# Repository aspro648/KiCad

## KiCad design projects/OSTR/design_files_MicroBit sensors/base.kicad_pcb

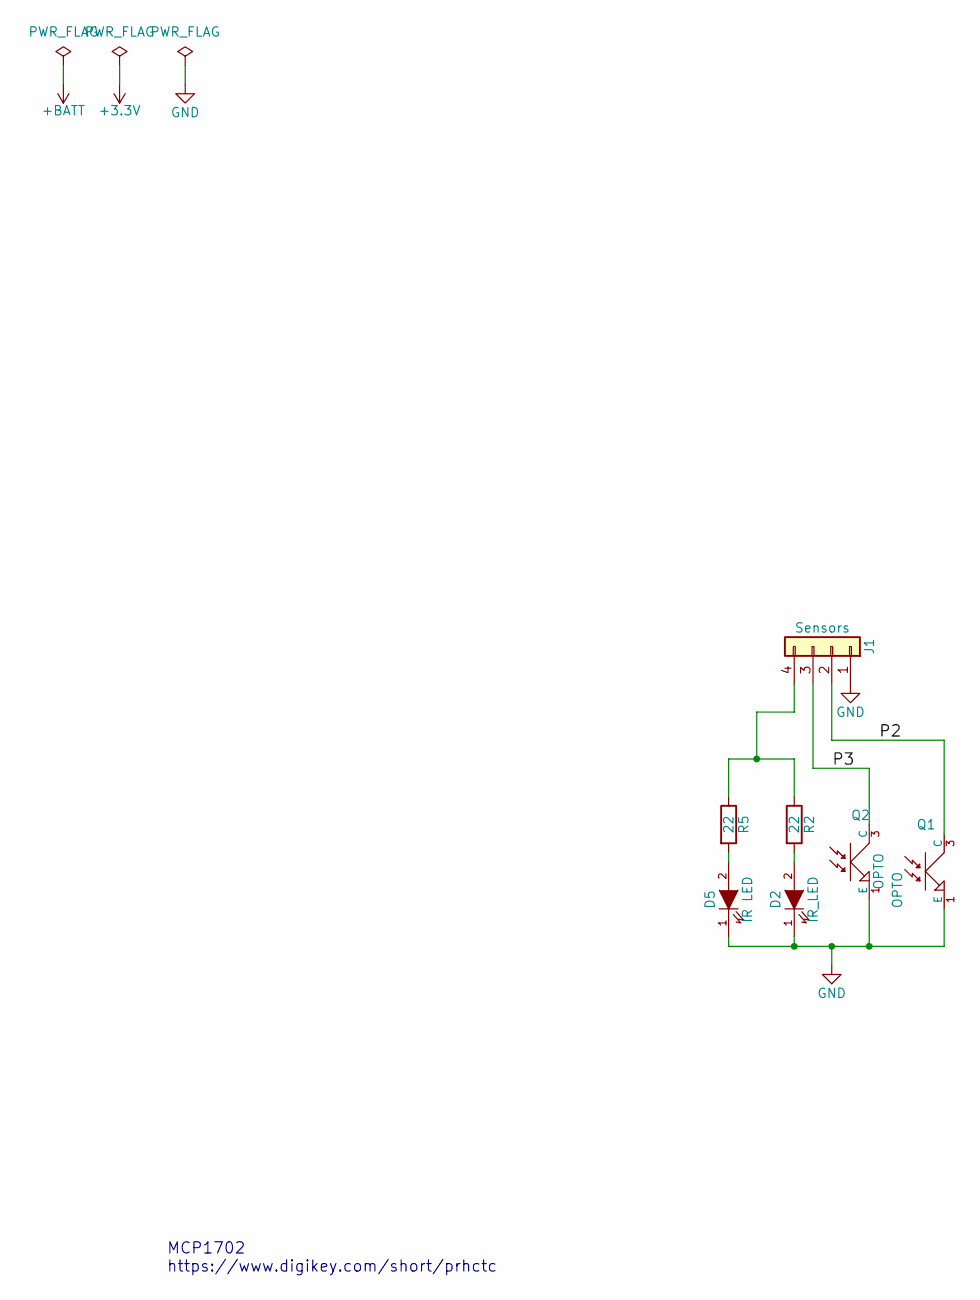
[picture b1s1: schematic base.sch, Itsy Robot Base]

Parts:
D2: IR_LED; LED-3MM
D5: IR LED; LED-3MM
J1: Sensors; Pin_Header_Straight_1x04_Pitch2.54mm
Q1, Q2: OPTO; PHOTOTRANS
R2, R5: 22; Resistor_Horz

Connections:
/P2: J1.2, Q1.3 (C)
/P3: J1.3, Q2.3 (C)
GND: D2.1 (K), D5.1 (K), J1.1, Q1.1 (E), Q2.1 (E)
unnamed: D2.2 (A), R2.2
unnamed: D5.2 (A), R5.2
unnamed: J1.4, R2.1, R5.1

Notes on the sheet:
MCP1702 https://www.digikey.com/short/prhctc

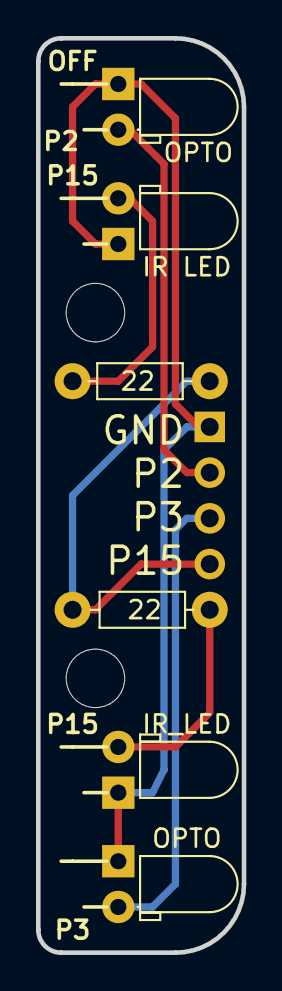
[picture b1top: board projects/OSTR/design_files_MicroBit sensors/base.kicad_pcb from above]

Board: 2 copper layers, 11.4 x 50.8 mm, 9 parts (1 on the bottom side), 6 nets.

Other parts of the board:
P9, P9#2: CONN_01X01; Lego_Pad

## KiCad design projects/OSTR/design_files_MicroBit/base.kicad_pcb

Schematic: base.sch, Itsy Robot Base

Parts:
C1: 100uF; C_Radial_D7.5_L11.2_P2.5
C2: 10uF; C_Radial_D5_L11_P2.5
C3, C4: 1uF; C_Disc_D3_P2.5
D1: D; D_A-405_P7.62mm_Horizontal
J1: microbit_edge_connector; MicroBit40
J2: BATT1; TerminalBlock_Pheonix_PT-3.5mm_2pol
J3: BATT2; TerminalBlock_Pheonix_PT-3.5mm_2pol
J4: LEFT_STEPPER; JST_B5B-XH-A
J5: RIGHT_STEPPER; JST_B5B-XH-A
J6: SERVO; Pin_Header_Straight_1x03
J7: TEST; Pin_Header_Straight_1x03_Pitch1.27mm
J8: Sensors; Pin_Header_Straight_1x04_Pitch2.54mm
J9: Sensors; Pin_Header_Angled_1x04_Pitch2.54mm
LS1: Speaker; SPEAKER
Q3: PNP; TO-126_Vertical
Q4: NPN; TO-92_Inline_Wide
R1: 10K; R__7.62mm
R2, R3: 1K; R__7.62mm
SW1: PWR; SW_Micro_SPST
U1: ULN2803; DIP-18_W7.62mm
U2: MCP1702; TO-92_Inline_Wide

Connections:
+3V3: C3.1, J1.17 (P18_3v3), J1.19 (3v3), J1.21 (3v3), J1.23 (3v3), J1.25 (3v3), J1.27 (P17_3v3), J7.2, Q4.3 (C), R1.2, U2.3 (VO)
/BAT: C4.1, D1.1 (K), J7.1, Q3.2, SW1.2, U2.2 (VI)
/P0: J1.71 (P0), J1.73 (P0), J1.75 (P0), J1.77 (P0), U1.1 (1B)
/P1: J1.55 (P1), J1.57 (P1), J1.59 (P1), J1.61 (P1), U1.4 (4B)
/P2: J1.37 (P2), J1.39 (P2), J1.41 (P2), J1.43 (P2), J8.2, J9.2
/P3: J1.79 (P3), J8.3, J9.3
/P4: J1.69 (P4), LS1.1
/P6: J1.65 (P6), U1.2 (2B)
/P7: J1.63 (P7), U1.3 (3B)
/P8: J1.53 (P8), U1.5 (5B)
/P9: J1.51 (P9), U1.6 (6B)
/P10: J1.49 (P10), U1.7 (7B)
/P12: J1.45 (P12)
/P13: J1.35 (P13_SCK), U1.8 (8B)
/P14: J1.33 (P14_MISO), R2.2
/P15: J1.31 (P15_MOSI), R3.2
/P16: J1.29 (P16), J6.1
GND: C1.2, C2.2, C3.2, C4.2, J1.1 (P22_GND), J1.3 (GND), J1.5 (GND), J1.7 (GND), J1.9 (GND), J1.11 (P21_GND), J2.1, J6.3, J7.3, J8.1, J9.1, LS1.2, U1.9 (GND), U2.1 (GND)
unnamed: C1.1, C2.1, D1.2 (A), J4.5, J5.5, J6.2, Q3.1, U1.10 (COM)
unnamed: J2.2, J3.1
unnamed: J3.2, SW1.1
unnamed: J4.1, U1.18 (1C)
unnamed: J4.2, U1.17 (2C)
unnamed: J4.3, U1.16 (3C)
unnamed: J4.4, U1.15 (4C)
unnamed: J5.1, U1.14 (5C)
unnamed: J5.2, U1.13 (6C)
unnamed: J5.3, U1.12 (7C)
unnamed: J5.4, U1.11 (8C)
unnamed: J8.4, J9.4, Q4.1 (E)
unnamed: Q3.3, R1.1, R3.1
unnamed: Q4.2 (B), R2.1

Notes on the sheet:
https://www.digikey.com/short/qcrr5m B5B-XH-A
- +
s + -
https://github.com/anthonykirby/kicad_microbit_connector
MCP1702 https://www.digikey.com/short/prhctc
2 coils energized per stepper = 850 mA, 5 W, 7 ohm
P0 - 1B P1 - 4B P2 - Sensor P3 - Sensor P4 - Speaker P5 - Button A P6 - 2B P7 - 3B P8 - 5B P9 - 6B P10- 7B P11- Button B P12 P13- 8B P14- Sensor Power P15- PNP? P16- Servo

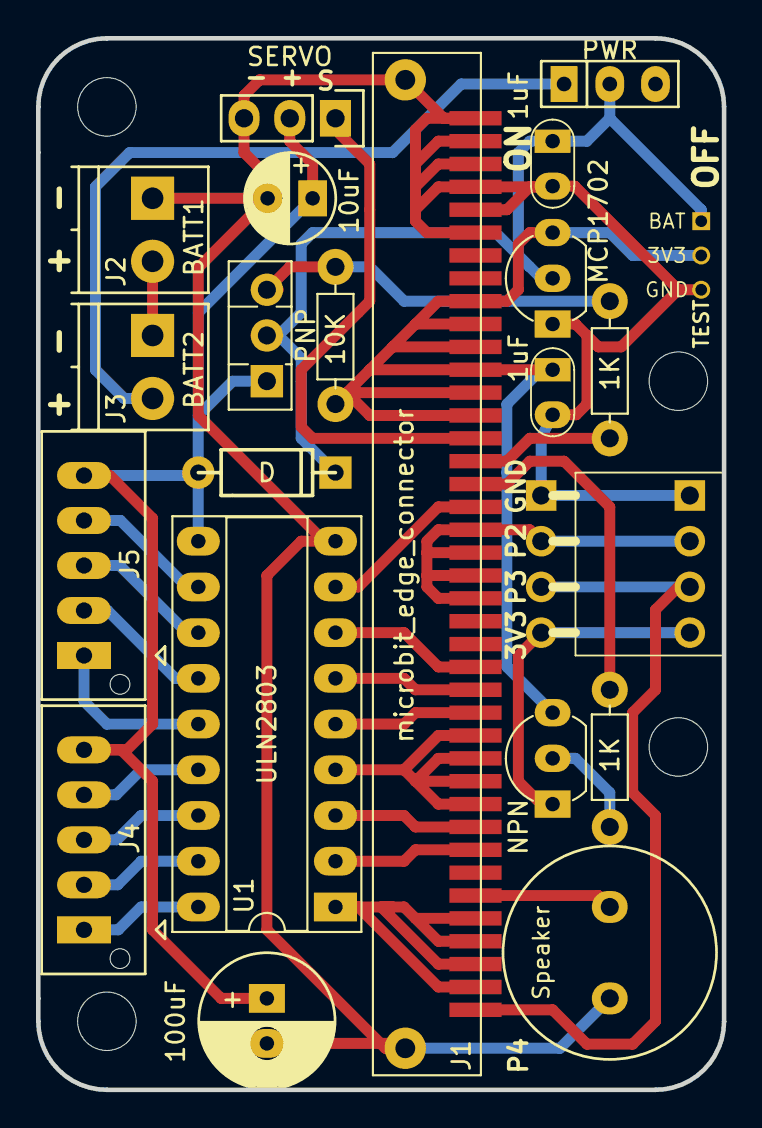
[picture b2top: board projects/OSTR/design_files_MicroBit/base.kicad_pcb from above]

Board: 2 copper layers, 38.1 x 58.4 mm, 29 parts (1 on the bottom side), 31 nets.

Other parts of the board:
P9, P9#2, P9#3, P9#4: CONN_01X01; Lego_Pad
VAL: MadeInOregonRev25
VAL#2: MB225rev

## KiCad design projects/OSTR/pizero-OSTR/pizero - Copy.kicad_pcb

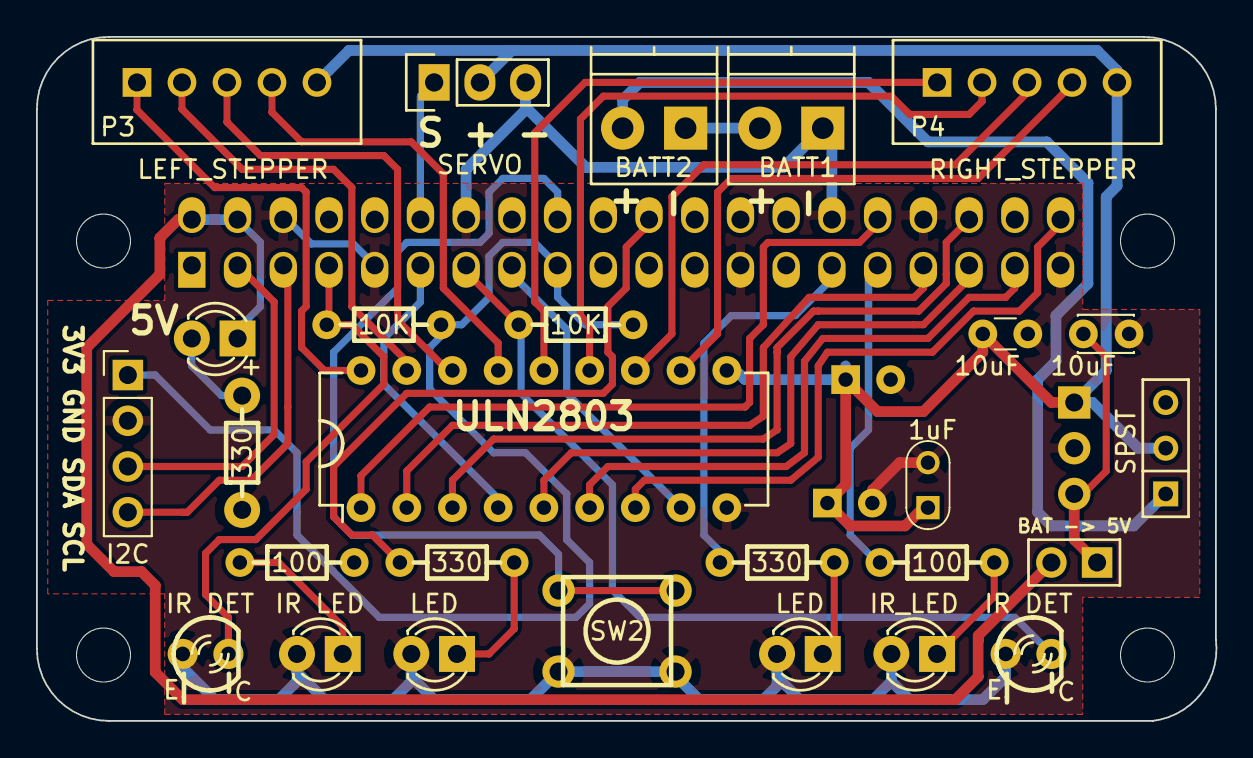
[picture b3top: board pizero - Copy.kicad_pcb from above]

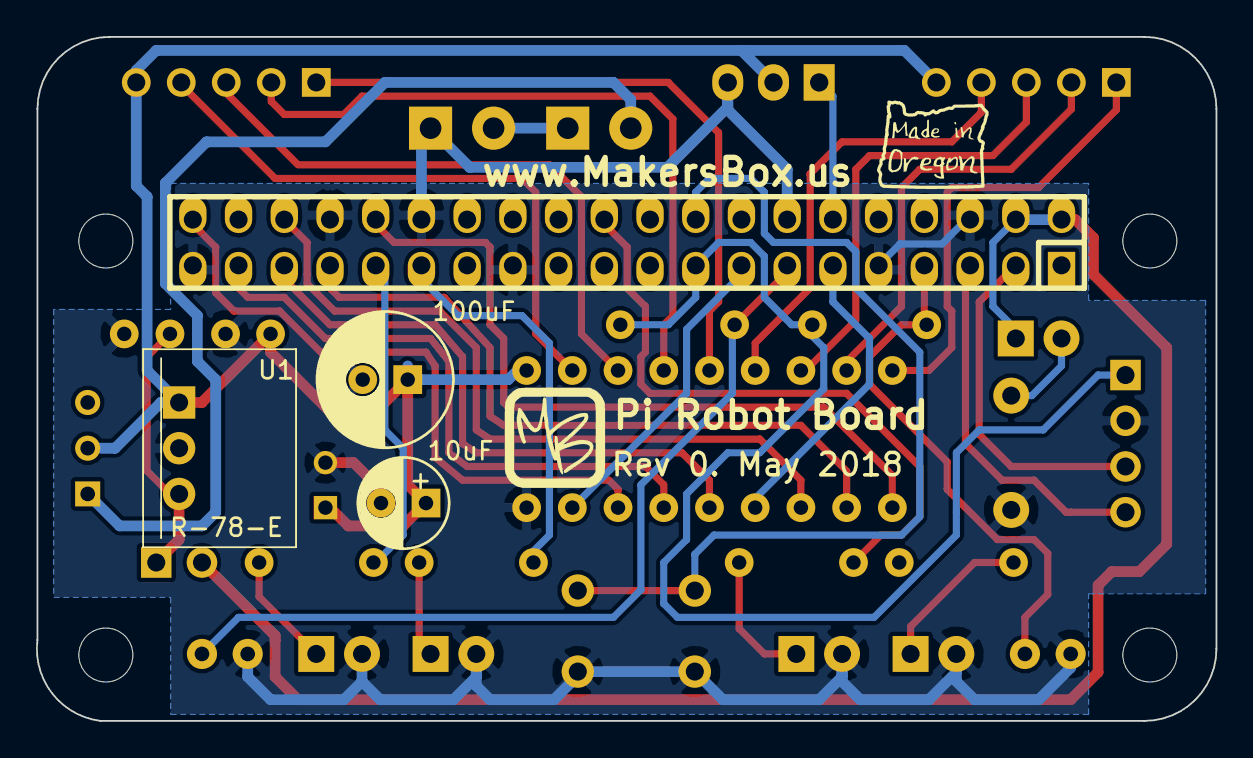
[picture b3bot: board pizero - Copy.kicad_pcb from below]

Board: 2 copper layers, 65.5 x 38.0 mm, 33 parts (3 on the bottom side), 37 nets.

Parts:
C1: 10uF; C_Disc_D3.0mm_W1.6mm_P2.50mm
C2: 10uF; C_Disc_D3.0mm_W2.0mm_P2.50mm
C3: 100uF; C_Radial_D7.5_L11.2_P2.5
C4: 10uF; C_Radial_D5_L11_P2.5
C5: 1uF; C_Disc_D3_P2.5
D1, D3, D4: LED; LED-3MM
D2: IR_LED; LED-3MM
D5: IR LED; LED-3MM
J1: I2C; Pin_Header_Straight_1x04_Pitch2.54mm
J2: JMP; Pin_Header_Straight_1x02_Pitch2.54mm
P0: Raspberry_Pi_+_Conn; pin_socket_20x2
P1: BATT1; TerminalBlock_Pheonix_PT-3.5mm_2pol
P2: BATT2; TerminalBlock_Pheonix_PT-3.5mm_2pol
P3: LEFT_STEPPER; JST_B5B-XH-A
P4: RIGHT_STEPPER; JST_B5B-XH-A
P5: SERVO; Pin_Header_Straight_1x03
Q1, Q2: OPTO_NPN; PHOTOTRANS
R1, R3, R4: 330; Resistor_Horz
R2, R5: 100; Resistor_Horz
R6, R7: 10K; Resistor_Horz
SW1: SPST; SW_Micro_SPST
SW2: SW_PUSH; SW_PUSH_SMALL
U1: R-78-E
U2: ULN2803; DIP-18_W7.62mm
VAL: MB225rev
VAL#2: MadeInOregonRev25

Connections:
+3V3: J1.1, P0.17, R6.2, R7.2
+5V: D1.2, J2.2, P0.2, P0.4
+BATT: C1.1, C3.1, C4.1, C5.1, P3.5, P4.5, P5.2, SW1.2, U1.1, U2.10
/GPIO4: P0.7, Q1.3, R6.1
/GPIO5: P0.29, R4.1
/GPIO6: P0.31, R2.1
/GPIO12: P0.32, U2.1
/GPIO13: P0.33, U2.2
/GPIO16: P0.36, U2.3
/GPIO17: P0.11, U2.4
/GPIO18: P0.12, P5.1
/GPIO19: P0.35, U2.5
/GPIO20: P0.37, U2.6
/GPIO21: P0.40, U2.7
/GPIO22: P0.15, U2.8
/GPIO24: P0.18, SW2.2
/GPIO25: P0.22, R3.1
/GPIO27: P0.13, Q2.3, R7.1
/SCL: J1.4, P0.5
/SDA: J1.3, P0.3
GND: C1.2, C2.2, C3.2, C4.2, C5.2, D2.1, D3.1, D4.1, D5.1, J1.2, P0.6, P0.9, P0.14, P0.25, P0.30, P0.34, P0.39, P1.1, P5.3, Q1.1, Q2.1, R1.2, SW2.1, U1.2, U2.9
unnamed: C2.1, J2.1, U1.3
unnamed: D1.1, R1.1
unnamed: D2.2, R2.2
unnamed: D3.2, R3.2
unnamed: D4.2, R4.2
unnamed: D5.2, R5.2
unnamed: P1.2, P2.1
unnamed: P2.2, SW1.1
unnamed: P3.1, U2.18
unnamed: P3.2, U2.17
unnamed: P3.3, U2.16
unnamed: P3.4, U2.15
unnamed: P4.1, U2.14
unnamed: P4.2, U2.13
unnamed: P4.3, U2.12
unnamed: P4.4, U2.11

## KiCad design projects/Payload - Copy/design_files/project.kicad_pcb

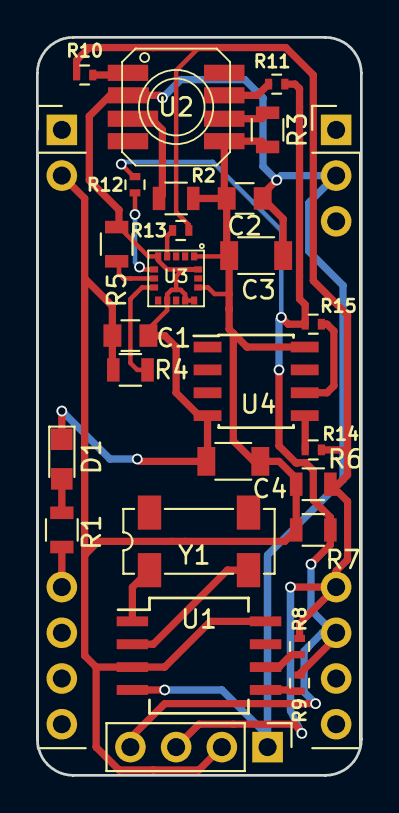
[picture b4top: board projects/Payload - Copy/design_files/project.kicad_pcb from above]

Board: 2 copper layers, 18.0 x 41.0 mm, 28 parts (0 on the bottom side), 20 nets.

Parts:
C1, C2: 0.1uF; C_0805
C3, C4: 10uF; C_1206
D1: LED; LED_0805
J1: Isty Left; Pin_Header_Straight_1x14_Pitch2.54mm
J2: Itsy Right; Pin_Header_Straight_1x14_Pitch2.54mm
J3: Display; Pin_Header_Straight_1x04_Pitch2.54mm
R1: 1K; R_0805
R2, R3, R4, R5: 10K; R_0805
R6, R7: 4K7; R_0805
R8, R9, R10, R11, R12, R13, R14, R15: 0; R_0402
U1: PCF8523; SO-8_5.3x6.2mm_Pitch1.27mm
U2: MS5803
U3: LIS3DH
U4: 24LC256; SOIC-8_3.9x4.9mm_Pitch1.27mm
Y1: 32.768 KHz; Crystal_SMD_SeikoEpson_MC306-4pin_8.0x3.2mm

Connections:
/D13: J1.11, R1.2
/SCL: J2.11, J3.3, R6.2, R8.1, R10.1, R13.1, R14.1
/SDA: J2.12, J3.4, R7.2, R9.1, R11.1, R12.2, R15.1
/SDO: R5.2, U3.7
GND: C1.2, C2.2, C3.2, C4.2, D1.1, J2.2, J3.1, R5.1, U1.4, U2.2, U3.5, U3.10, U3.12, U3.13, U3.16, U4.4
unnamed: D1.2, R1.1
unnamed: R2.1, U2.3
unnamed: R3.1, U2.6
unnamed: R4.2, U3.8
unnamed: R8.2, U1.6
unnamed: R9.2, U1.5
unnamed: R10.2, U2.1
unnamed: R11.2, U2.7
unnamed: R12.1, U3.6
unnamed: R13.2, U3.4
unnamed: R14.2, U4.5
unnamed: R15.2, U4.6
unnamed: U1.1, Y1.1
unnamed: U1.2, Y1.2
VCC: C1.1, C2.1, C3.1, C4.1, J1.2, J3.2, R2.2, R3.2, R4.1, R6.1, R7.1, U1.3, U1.8, U2.5, U3.1, U3.14, U4.8

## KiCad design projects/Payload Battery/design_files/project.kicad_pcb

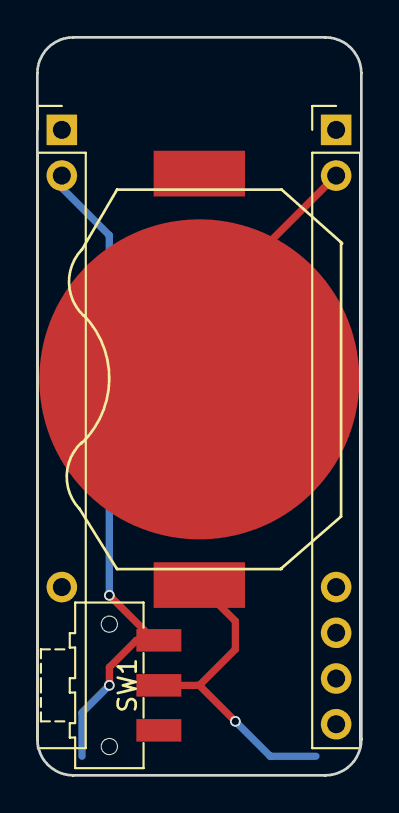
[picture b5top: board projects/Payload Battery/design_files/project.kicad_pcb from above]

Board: 2 copper layers, 18.0 x 41.0 mm, 5 parts (1 on the bottom side), 3 nets.

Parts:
BT1: Battery_Cell; BATT_CR2032_SMD
J1: Isty Left; Pin_Header_Straight_1x14_Pitch2.54mm
J2: Itsy Right; Pin_Header_Straight_1x14_Pitch2.54mm
SW1: SW_SPDT; SW_SPDT_CK-JS102011SAQN
SW2: SW_Reed; REED_SWITCH

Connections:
GND: BT1.2, J2.2
unnamed: BT1.1, SW1.2, SW2.2
VCC: J1.2, SW1.1, SW2.1

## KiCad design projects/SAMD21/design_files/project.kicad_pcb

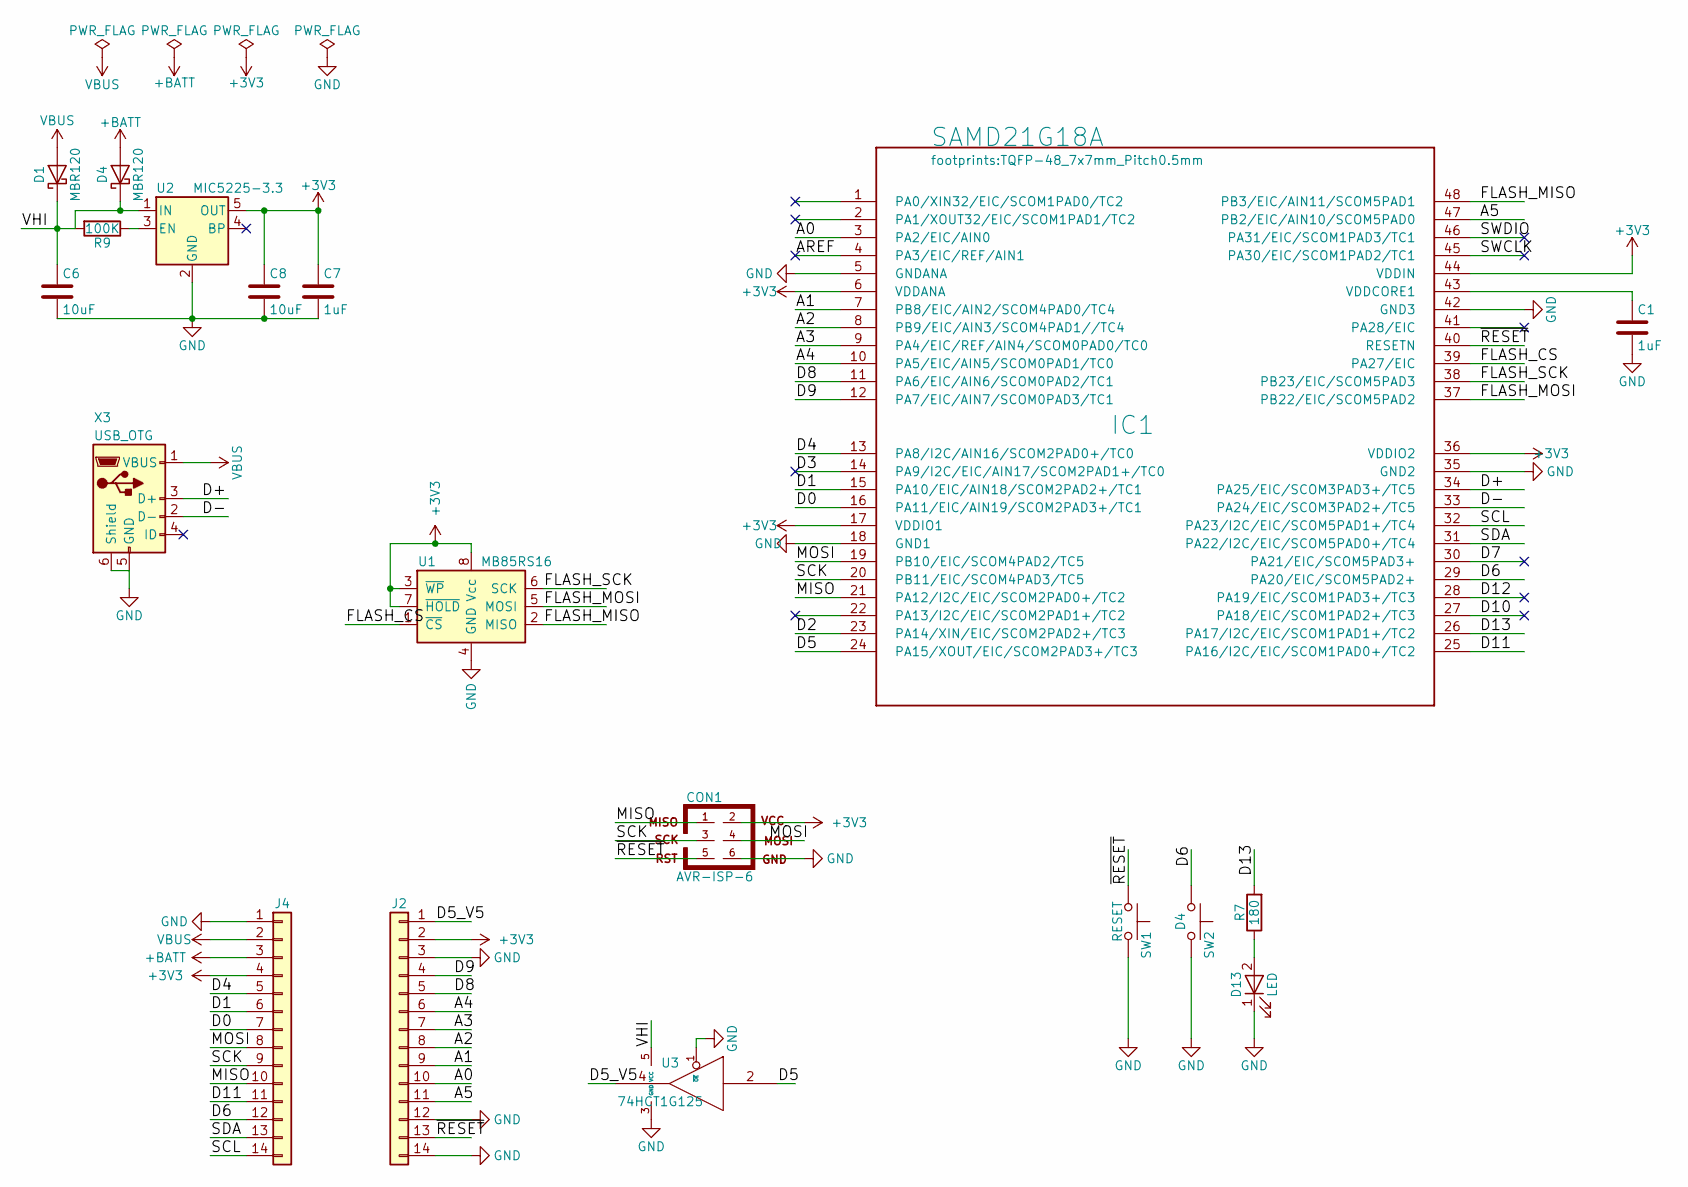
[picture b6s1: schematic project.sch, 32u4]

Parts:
C1, C7: 1uF; C_0603
C6, C8: 10uF; C_0805
CON1: AVR-ISP-6
D1, D4: MBR120; D_SOD-123F
D13: LED; LED_0603
IC1: SAMD21G18A; TQFP-48_7x7mm_Pitch0.5mm
J2, J4: Conn_01x14; Pin_Header_Straight_1x14_Pitch2.54mm
R7: 180; R_0603
R9: 100K; R_0603
SW1: RESET; SW_SPST_KMR2
SW2: D4; SW_SPST_KMR2
U1: MB85RS16; SOIC-8_3.9x4.9mm_Pitch1.27mm
U2: MIC5225-3.3; SOT-23-5
U3: 74HCT1G125; TSOP-5_1.65x3.05mm_Pitch0.95mm
X3: USB_OTG; USB_Micro-B_Molex-105017-0001

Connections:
+3V3: C7.1, C8.1, CON1.2, IC1.6 (VDDANA), IC1.17 (VDDIO1), IC1.36 (VDDIO2), IC1.44 (VDDIN), J2.2, J4.4, U1.3 (~WP), U1.7 (~HOLD), U1.8 (Vcc), U2.5 (OUT)
+BATT: D4.2 (A), J4.3
/A0: IC1.3 (PA2/EIC/AIN0), J2.10
/A1: IC1.7 (PB8/EIC/AIN2/SCOM4PAD0/TC4), J2.9
/A2: IC1.8 (PB9/EIC/AIN3/SCOM4PAD1//TC4), J2.8
/A3: IC1.9 (PA4/EIC/REF/AIN4/SCOM0PAD0/TC0), J2.7
/A4: IC1.10 (PA5/EIC/AIN5/SCOM0PAD1/TC0), J2.6
/A5: IC1.47 (PB2/EIC/AIN10/SCOM5PAD0), J2.11
/AREF: IC1.4 (PA3/EIC/REF/AIN1)
/D0: IC1.16 (PA11/EIC/AIN19/SCOM2PAD3+/TC1), J4.7
/D1: IC1.15 (PA10/EIC/AIN18/SCOM2PAD2+/TC1), J4.6
/D2: IC1.23 (PA14/XIN/EIC/SCOM2PAD2+/TC3)
/D3: IC1.14 (PA9/I2C/EIC/AIN17/SCOM2PAD1+/TC0)
/D4: IC1.13 (PA8/I2C/AIN16/SCOM2PAD0+/TC0), J4.5
/D5: IC1.24 (PA15/XOUT/EIC/SCOM2PAD3+/TC3), U3.2
/D5_V5: J2.1, U3.4
/D6: IC1.29 (PA20/EIC/SCOM5PAD2+), J4.12, SW2.1
/D7: IC1.30 (PA21/EIC/SCOM5PAD3+)
/D8: IC1.11 (PA6/EIC/AIN6/SCOM0PAD2/TC1), J2.5
/D9: IC1.12 (PA7/EIC/AIN7/SCOM0PAD3/TC1), J2.4
/D10: IC1.27 (PA18/EIC/SCOM1PAD2+/TC3)
/D11: IC1.25 (PA16/I2C/EIC/SCOM1PAD0+/TC2), J4.11
/D12: IC1.28 (PA19/EIC/SCOM1PAD3+/TC3)
/D13: IC1.26 (PA17/I2C/EIC/SCOM1PAD1+/TC2), R7.2
/D+: IC1.34 (PA25/EIC/SCOM3PAD3+/TC5), X3.3 (D+)
/D-: IC1.33 (PA24/EIC/SCOM3PAD2+/TC5), X3.2 (D-)
/FLASH_CS: IC1.39 (PA27/EIC), U1.1 (~CS)
/FLASH_MISO: IC1.48 (PB3/EIC/AIN11/SCOM5PAD1), U1.2 (MISO)
/FLASH_MOSI: IC1.37 (PB22/EIC/SCOM5PAD2), U1.5 (MOSI)
/FLASH_SCK: IC1.38 (PB23/EIC/SCOM5PAD3), U1.6 (SCK)
/MISO: CON1.1, IC1.21 (PA12/I2C/EIC/SCOM2PAD0+/TC2), J4.10
/MOSI: CON1.4, IC1.19 (PB10/EIC/SCOM4PAD2/TC5), J4.8
/SCK: CON1.3, IC1.20 (PB11/EIC/SCOM4PAD3/TC5), J4.9
/SCL: IC1.32 (PA23/I2C/EIC/SCOM5PAD1+/TC4), J4.14
/SDA: IC1.31 (PA22/I2C/EIC/SCOM5PAD0+/TC4), J4.13
/SWCLK: IC1.45 (PA30/EIC/SCOM1PAD2/TC1)
/SWDIO: IC1.46 (PA31/EIC/SCOM1PAD3/TC1)
/VHI: C6.1, D1.1 (K), D4.1 (K), R9.2, U2.1 (IN), U3.5 (VCC)
/~RESET: CON1.5, IC1.40 (RESETN), J2.13, SW1.1
GND: C1.2, C6.2, C7.2, C8.2, CON1.6, D13.1 (K), IC1.5 (GNDANA), IC1.18 (GND1), IC1.35 (GND2), IC1.42 (GND3), J2.3, J2.12, J2.14, J4.1, SW1.2, SW2.2, U1.4 (GND), U2.2 (GND), U3.1 (~OE), U3.3 (GND), X3.5 (GND), X3.6 (Shield)
unnamed: C1.1, IC1.43 (VDDCORE1)
unnamed: D13.2 (A), R7.1
unnamed: R9.1, U2.3 (EN)
VBUS: D1.2 (A), J4.2, X3.1 (VBUS)

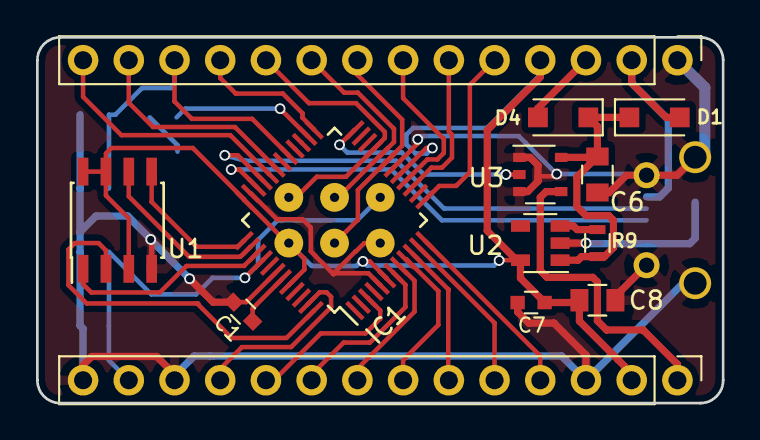
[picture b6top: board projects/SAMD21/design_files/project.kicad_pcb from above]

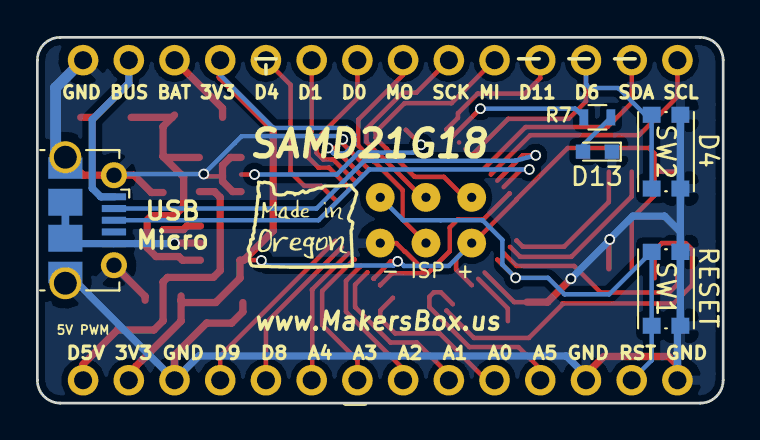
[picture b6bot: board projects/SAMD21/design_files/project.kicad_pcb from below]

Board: 2 copper layers, 38.1 x 20.3 mm, 20 parts (6 on the bottom side), 36 nets.

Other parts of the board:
VAL: MadeInOregonRev25

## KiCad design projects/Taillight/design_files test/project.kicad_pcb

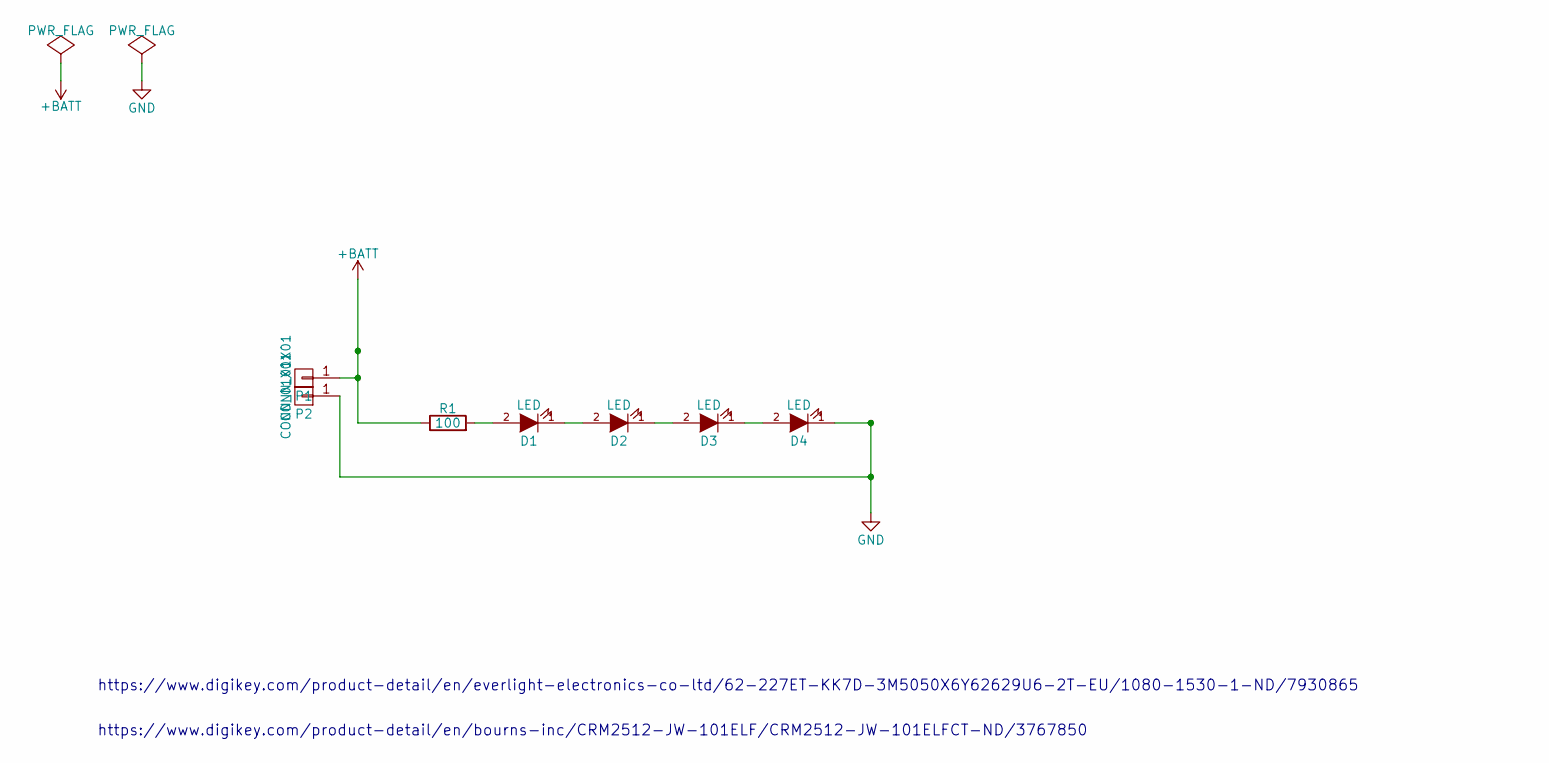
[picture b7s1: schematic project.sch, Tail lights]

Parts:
D1, D2, D3, D4: LED; LED-5630
P1, P2: CONN_01X01; SolderWirePad_single_2mmDrill
R1: 100; R_2512

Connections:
+BATT: P1.1, R1.1
GND: D4.1 (K), P2.1
unnamed: D1.1 (K), D2.2 (A)
unnamed: D1.2 (A), R1.2
unnamed: D2.1 (K), D3.2 (A)
unnamed: D3.1 (K), D4.2 (A)

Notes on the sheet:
https://www.digikey.com/product-detail/en/everlight-electronics-co-ltd/62-227ET-KK7D-3M5050X6Y62629U6-2T-EU/1080-1530-1-ND/7930865
https://www.digikey.com/product-detail/en/bourns-inc/CRM2512-JW-101ELF/CRM2512-JW-101ELFCT-ND/3767850

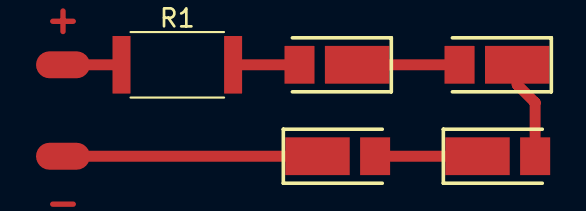
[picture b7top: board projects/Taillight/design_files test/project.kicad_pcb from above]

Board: 2 copper layers, 7 parts (0 on the bottom side), 6 nets.

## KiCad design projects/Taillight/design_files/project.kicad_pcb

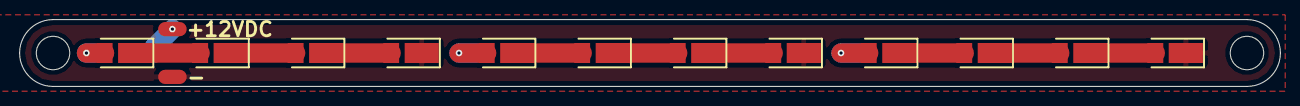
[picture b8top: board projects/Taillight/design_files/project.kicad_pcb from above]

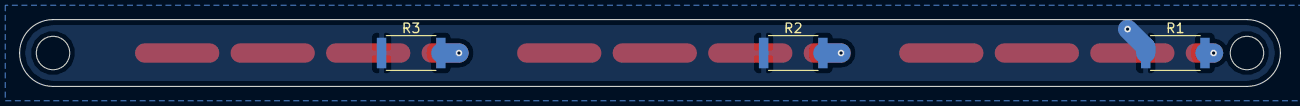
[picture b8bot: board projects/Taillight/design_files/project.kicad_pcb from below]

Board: 2 copper layers, 132.0 x 7.0 mm, 17 parts (3 on the bottom side), 14 nets.

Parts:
D1, D2, D3, D4, D5, D6, D7, D8, D9, D10, D11, D12: LED; LED-5630
P1, P2: CONN_01X01; SolderWirePad_single_2mmDrill
R1, R2, R3: 100; R_2512

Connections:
+BATT: P1.1, R1.1, R2.1, R3.1
GND: D4.1, D8.1, D12.1, P2.1
unnamed: D1.1, D2.2
unnamed: D1.2, R1.2
unnamed: D2.1, D3.2
unnamed: D3.1, D4.2
unnamed: D5.1, D6.2
unnamed: D5.2, R2.2
unnamed: D6.1, D7.2
unnamed: D7.1, D8.2
unnamed: D9.2, R3.2
unnamed: D10.1, D11.2
unnamed: D9.1, D10.2
unnamed: D11.1, D12.2

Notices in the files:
projects/OSTR/pizero-OSTR/pizero - Copy.kicad_pcb:
License: CERN OHL V1.2
